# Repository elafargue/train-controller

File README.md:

train-controller
================

A Z scale model train controller with web interface.

You will find detailed instructions at http://www.aerodynes.org/ . This repository includes both hardware design files and the software you need to build the complete project.

The whole system is working well, and has been running for a long time on an actual layout.

Repository structure:

arduino: arduino sketches for the train controller hardware
hardware: schematics, boards (Eagle)
server: the node.js server that interfaces with the controller and serves the web app

Installation:

Please refer to http://www.aerodynes.org/ for detailed installation instructions. Below is a quick summary:

- Build the cape - Eagle files are included, all components are referenced in the design file, it is fairly straightforward.
- Install the arduino firmware on the cape: you can use the very good "ino" command line interface for doing so.
- Install Ubuntu Linux on your Beaglebone Black
- Install the latest nodejs distribution, and clone this repository
- Install mongodb (Ubuntu package is fine)
- Run "npm install" then "node server.js"
- ... you should be set!

Credits:

Thanks to the creators of the PID and aJson libraries (be sure to use the latest aJson library as I contributed patches to make it more robust).
Thanks to Christophe Coenraets for his great tutorials which were used as a base for the server

License:

All original code is placed under GPLv3 unless stated otherwise, see relevant license files where appropriate.

# Run as a service

Use `resources/train-controller.service` and copy it to `/etc/systemd/system`, then:

```
$ sudo systemctl daemon-reload
$ sudo systemctl enable train-controller
Created symlink /etc/systemd/system/multi-user.target.wants/train-controller.service → /etc/systemd/system/train-controller.service.
$ sudo service train-controller start
```

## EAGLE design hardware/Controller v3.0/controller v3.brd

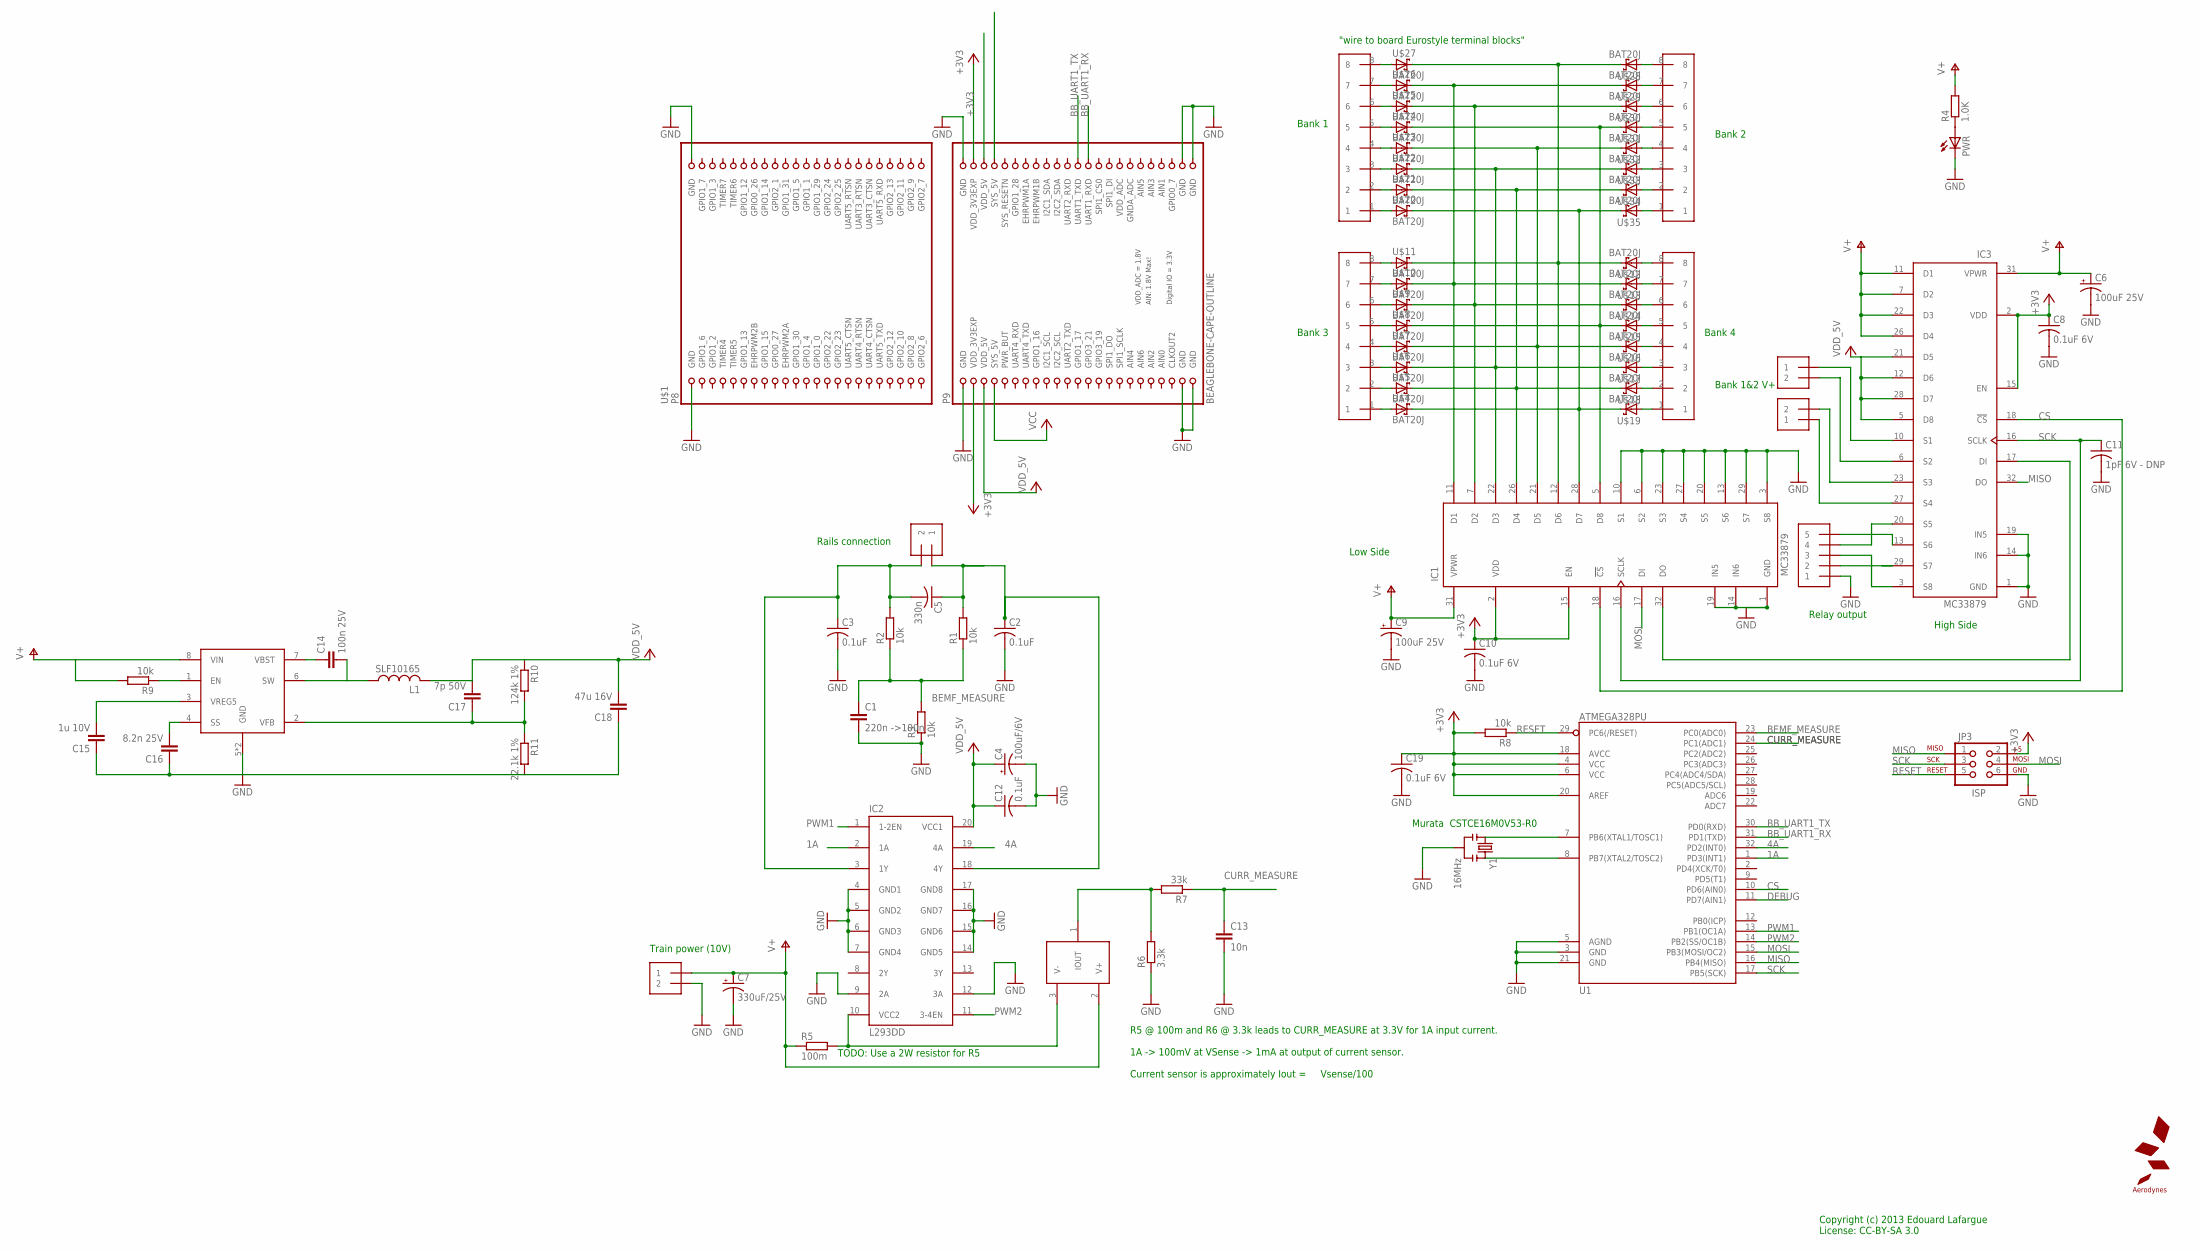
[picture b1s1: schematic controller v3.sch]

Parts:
BANK12, BANK34: 1X2-3.5MM
C1: 220n ->100n; C0805
C2, C3, C12: 0.1uF; C025-025X050
C4: 100uF/6V; E2,5-5
C5: 330n; C050-025X075
C6, C9: 100uF 25V; E2,5-6E
C7: 330uF/25V; E3,5-8
C8, C10: 0.1uF 6V; C025-025X050
C11: 1pF 6V - DNP; C0805K
C13: 10n; C0805K
C14: 100n 25V; C0805K
C15: 1u 10V; C0603K
C16: 8.2n 25V; C0603K
C17: 7p 50V; C0805K
C18: 47u 16V; C1210K
C19: 0.1uF 6V; C0603K
CON1, CON2, CON3, CON4: 1X08-CONN3.5MM; 1X08-3.5MM
CUR_SENSE: ZXCT1009-F; SOT23-1TOP
IC1, IC3: MC33879; 32SOICW-EP-065PITCH
IC2: L293DD; SOIC20-2
J1: 1X5; 1X05-3.5MM
JP3: ISP; 2X3
L1: SLF10165
PWR: LED3MM
R1, R2, R3, R8, R9: 10k; R0603
R4: 1.0K; R0603
R5: 100m; M1206
R6: 3.3k; R0603
R7: 33k; R0603
R10: 124k 1%; R0603
R11: 22.1k 1%; R0603
SL1, SL2: 1X2-3.5MM
U1: ATMEGA328PU; TQFP32-08
U$1: BEAGLEBONE-CAPE-OUTLINE; BEAGLEBONE_NOCUT
U$2: LOGO-AERODYNESSMALL; LOGO-AERODYNES-S
U$4, U$5, U$6, U$7, U$8, U$9, U$10, U$11, U$12, U$13, U$14, U$15, U$16, U$17, U$18, U$19, U$20, U$21, U$22, U$23, U$24, U$25, U$26, U$27, U$28, U$29, U$30, U$31, U$32, U$33, U$34, U$35: BAT20J; SOD-323F
U$36: TPS54327DDA; SOIC8-DDA
Y1: 16MHz; RESONATOR-SMD

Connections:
1A: IC2.2 (1A), U1.1 (PD3(INT1))
1Y: C3.1, C5.2, IC2.3 (1Y), R2.2, SL1.2
4A: IC2.19 (4A), U1.32 (PD2(INT0))
4Y: C2.1, C5.1, IC2.18 (4Y), R1.2, SL1.1
+3V3: C8.1, C10.1, C19.1, IC1.2 (VDD), IC1.15 (EN), IC3.2 (VDD), IC3.15 (EN), JP3.2, R8.2, U1.4 (VCC), U1.6 (VCC), U1.18 (AVCC), U1.20 (AREF), U$1.P9-3 (VDD_3V3EXP), U$1.P9-4 (VDD_3V3EXP)
BB_UART1_RX: U1.31 (PD1(TXD)), U$1.P9-26 (UART1_RXD)
BB_UART1_TX: U1.30 (PD0(RXD)), U$1.P9-24 (UART1_TXD)
BEMF_MEASURE: C1.1, R1.1, R2.1, R3.2, U1.23 (PC0(ADC0))
CS: IC1.18 (!CS), IC3.18 (!CS), U1.10 (PD6(AIN0))
CURR_MEASURE: C13.1, R7.1, U1.24 (PC1(ADC1))
DEBUG: U1.11 (PD7(AIN1))
GND: C1.2, C2.2, C3.2, C4.-, C6.-, C7.-, C8.2, C9.-, C10.2, C11.2, C12.2, C13.2, C15.1, C16.1, C18.1, C19.2, IC1.1 (GND), IC1.3 (S8), IC1.6 (S2), IC1.10 (S1), IC1.13 (S6), IC1.14 (IN6), IC1.19 (IN5), IC1.20 (S5), IC1.23 (S3), IC1.27 (S4), IC1.29 (S7), IC2.4 (GND1), IC2.5 (GND2), IC2.6 (GND3), IC2.7 (GND4), IC2.9 (2A), IC2.12 (3A), IC2.14 (GND5), IC2.15 (GND6), IC2.16 (GND7), IC2.17 (GND8), IC3.1 (GND), IC3.14 (IN6), IC3.19 (IN5), J1.1, JP3.6, PWR.K (C), R3.1, R6.1, R11.2, SL2.2, U1.3 (GND), U1.5 (AGND), U1.21 (GND), U$1.P8-1 (GND), U$1.P8-2 (GND), U$1.P9-1 (GND), U$1.P9-2 (GND), U$1.P9-43 (GND), U$1.P9-44 (GND), U$1.P9-45 (GND), U$1.P9-46 (GND), U$36.5 (GND), U$36.PAD (GND), Y1.2
GNDA_ADC: U$1.P9-34 (GNDA_ADC)
MISO: IC3.32 (DO), JP3.1, U1.16 (PB4(MISO))
MOSI: IC1.17 (DI), JP3.4, U1.15 (PB3(MOSI/OC2))
unnamed: BANK34.1, IC3.27 (S4)
unnamed: BANK34.2, IC3.23 (S3)
unnamed: BANK12.2, IC3.6 (S2)
unnamed: BANK12.1, IC3.10 (S1)
unnamed: CUR_SENSE.3 (V-), IC2.10 (VCC2), R5.2
unnamed: CUR_SENSE.1 (IOUT), R6.2, R7.2
unnamed: IC1.22 (D3), U$6.C, U$17.C, U$22.C, U$33.C
unnamed: IC1.21 (D5), U$7.C, U$16.C, U$23.C, U$32.C
unnamed: IC1.5 (D8), U$8.C, U$15.C, U$24.C, U$31.C
unnamed: CON3.3, U$6.A
unnamed: IC1.28 (D7), U$4.C, U$19.C, U$20.C, U$35.C
unnamed: IC1.12 (D6), U$11.C, U$12.C, U$27.C, U$28.C
unnamed: IC1.32 (DO), IC3.17 (DI)
unnamed: IC1.11 (D1), U$10.C, U$13.C, U$26.C, U$29.C
unnamed: IC1.26 (D4), U$5.C, U$18.C, U$21.C, U$34.C
unnamed: IC1.7 (D2), U$9.C, U$14.C, U$25.C, U$30.C
unnamed: IC3.20 (S5), J1.4
unnamed: CON3.2, U$5.A
unnamed: CON3.1, U$4.A
unnamed: CON3.8, U$11.A
unnamed: CON3.7, U$10.A
unnamed: CON3.6, U$9.A
unnamed: CON3.5, U$8.A
unnamed: CON3.4, U$7.A
unnamed: CON4.8, U$12.A
unnamed: CON4.7, U$13.A
unnamed: CON4.6, U$14.A
unnamed: CON4.5, U$15.A
unnamed: CON4.4, U$16.A
unnamed: CON4.3, U$17.A
unnamed: CON4.2, U$18.A
unnamed: CON4.1, U$19.A
unnamed: CON1.8, U$27.A
unnamed: CON1.7, U$26.A
unnamed: PWR.A, R4.1
unnamed: CON1.6, U$25.A
unnamed: CON1.5, U$24.A
unnamed: CON1.4, U$23.A
unnamed: CON1.3, U$22.A
unnamed: CON1.2, U$21.A
unnamed: CON1.1, U$20.A
unnamed: CON2.8, U$28.A
unnamed: CON2.7, U$29.A
unnamed: CON2.6, U$30.A
unnamed: CON2.5, U$31.A
unnamed: CON2.4, U$32.A
unnamed: CON2.3, U$33.A
unnamed: CON2.2, U$34.A
unnamed: CON2.1, U$35.A
unnamed: IC3.13 (S6), J1.5
unnamed: IC3.29 (S7), J1.2
unnamed: IC3.3 (S8), J1.3
unnamed: U1.7 (PB6(XTAL1/TOSC1)), Y1.1
unnamed: U1.8 (PB7(XTAL2/TOSC2)), Y1.3
unnamed: R9.1, U$36.1 (EN)
unnamed: C14.1, U$36.7 (VBST)
unnamed: C16.2, U$36.4 (SS)
unnamed: C14.2, L1.P$1 (1), U$36.6 (SW)
unnamed: C15.2, U$36.3 (VREG5)
unnamed: C17.1, R10.2, R11.1, U$36.2 (VFB)
PWM1: IC2.1 (1-2EN), U1.13 (PB1(OC1A))
PWM2: IC2.11 (3-4EN), U1.14 (PB2(SS/OC1B))
RESET: JP3.5, R8.1, U1.29 (PC6(/RESET))
SCK: C11.1, IC1.16 (SCLK), IC3.16 (SCLK), JP3.3, U1.17 (PB5(SCK))
SYS_5V: U$1.P9-7 (SYS_5V), U$1.P9-8 (SYS_5V)
V+: C6.+, C7.+, C9.+, CUR_SENSE.2 (V+), IC1.31 (VPWR), IC3.7 (D2), IC3.11 (D1), IC3.22 (D3), IC3.26 (D4), IC3.31 (VPWR), R4.2, R5.1, R9.2, SL2.1, U$36.8 (VIN)
VDD_5V: C4.+, C12.1, C17.2, C18.2, IC2.20 (VCC1), IC3.5 (D8), IC3.12 (D6), IC3.21 (D5), IC3.28 (D7), L1.P$2 (2), R10.1, U$1.P9-5 (VDD_5V), U$1.P9-6 (VDD_5V)
VDD_ADC: U$1.P9-32 (VDD_ADC)

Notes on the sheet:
Rails connection
Train power (10V)
Low Side
High Side
Bank 1
Bank 2
Bank 1&2 V+
Bank 3
Bank 4
"wire to board Eurostyle terminal blocks"
R5 @ 100m and R6 @ 3.3k leads to CURR_MEASURE at 3.3V for 1A input current. 1A -> 100mV at VSense -> 1mA at output of current sensor. Current sensor is approximately Iout = Vsense/100
Copyright (c) 2013 Edouard Lafargue License: CC-BY-SA 3.0
TODO: Use a 2W resistor for R5
Relay output
Murata CSTCE16M0V53-R0

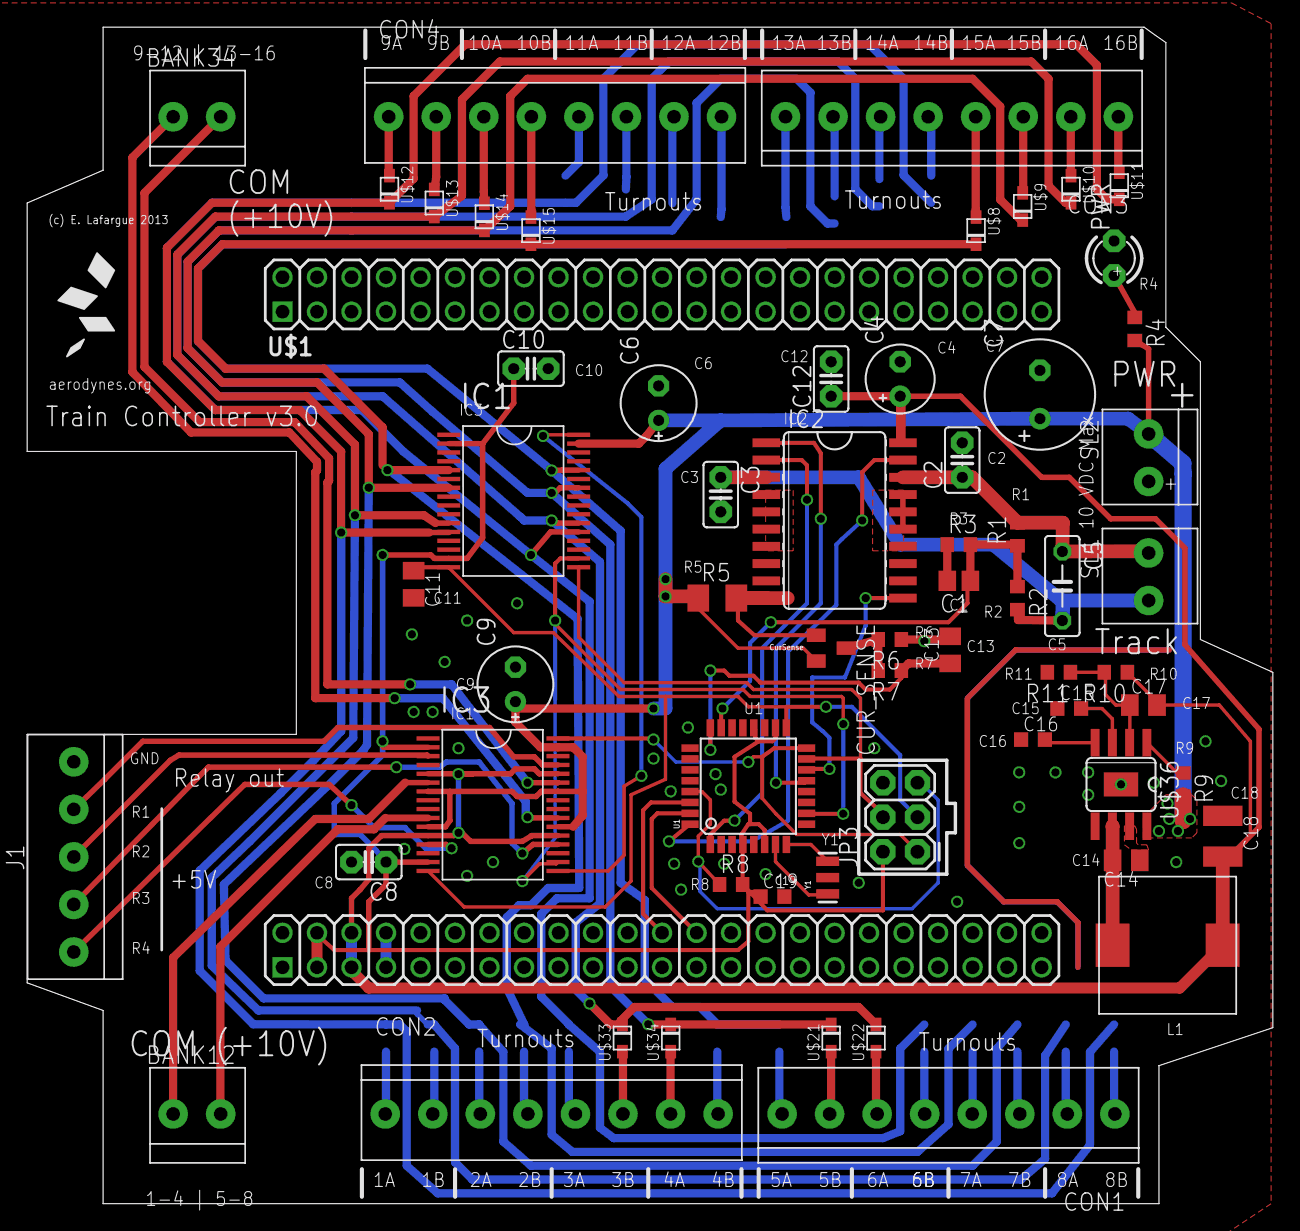
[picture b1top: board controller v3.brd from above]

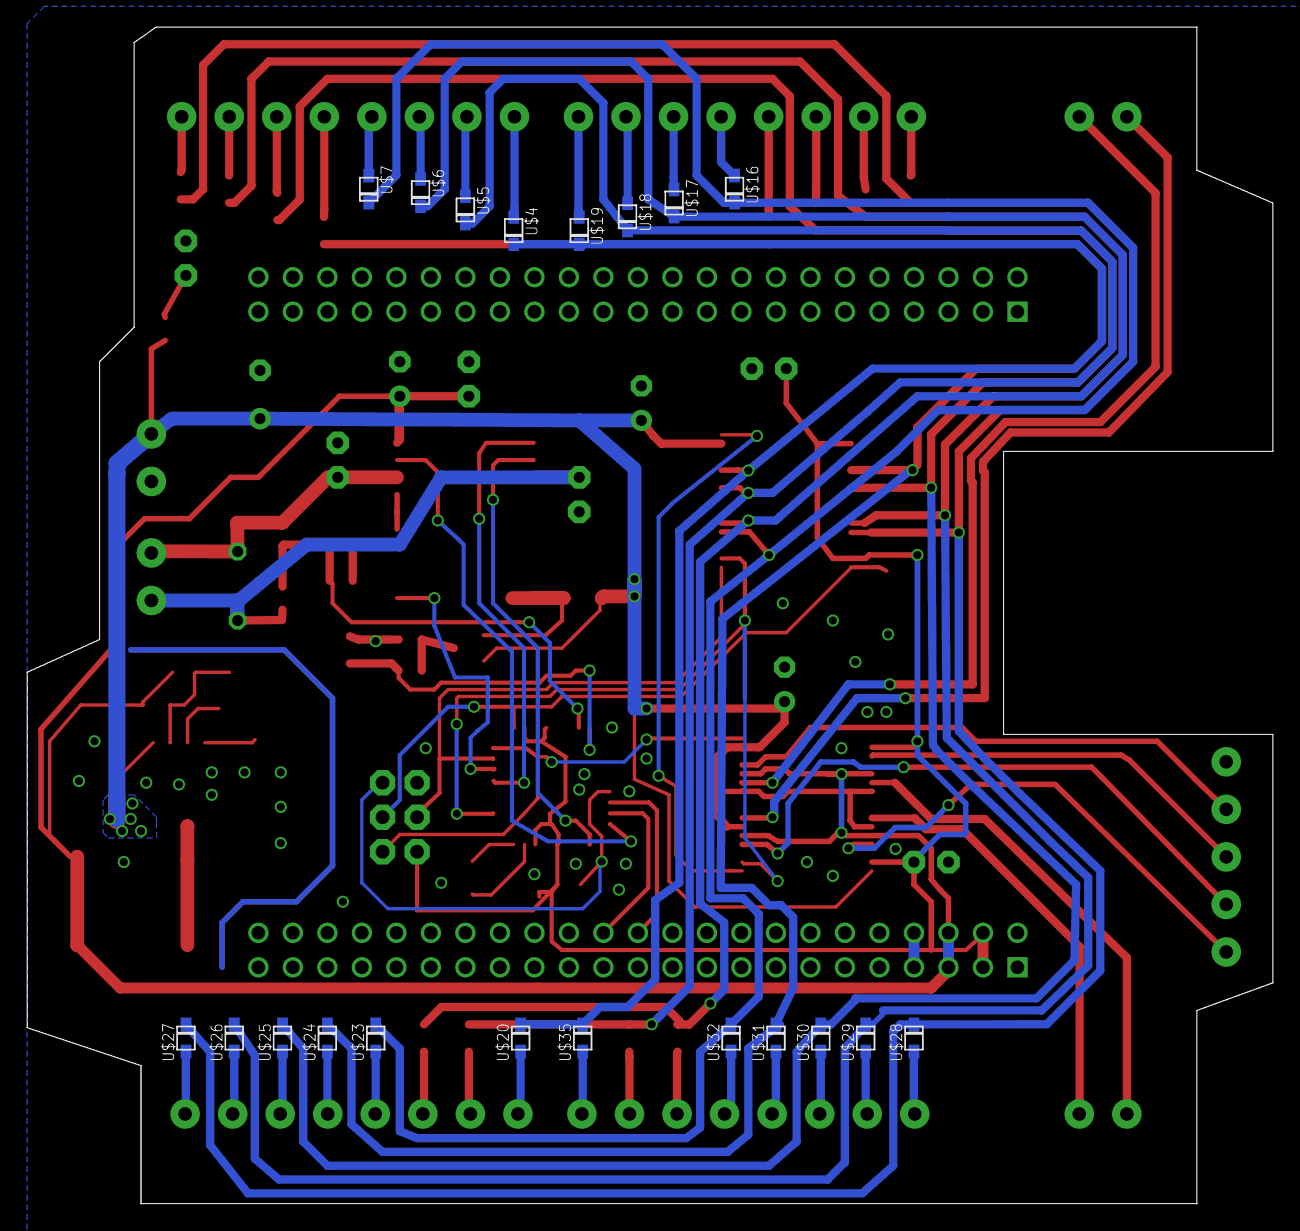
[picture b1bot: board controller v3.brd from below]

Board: 2 copper layers, 91.7 x 86.6 mm, 83 parts (20 on the bottom side), 80 nets.

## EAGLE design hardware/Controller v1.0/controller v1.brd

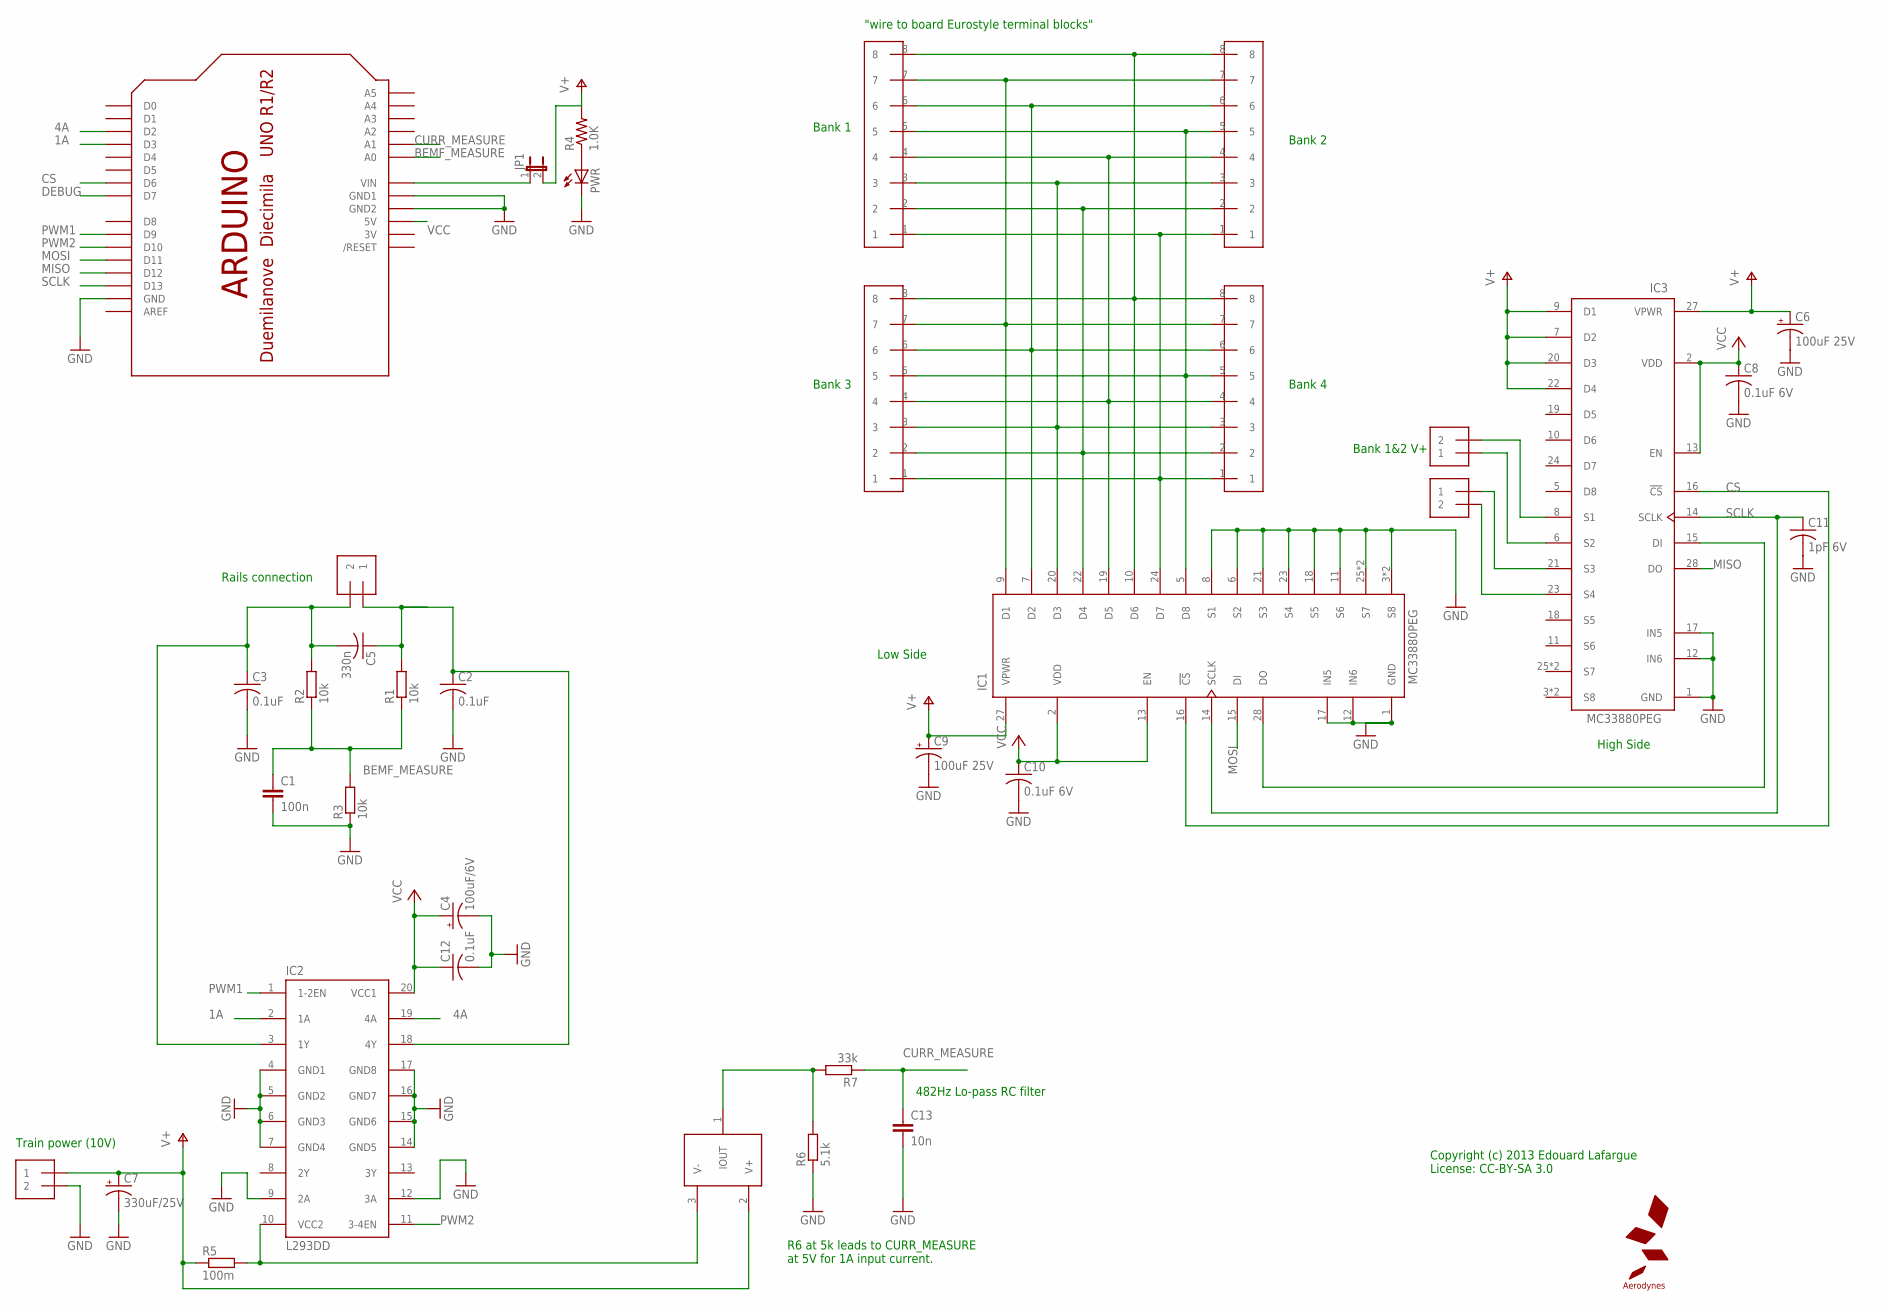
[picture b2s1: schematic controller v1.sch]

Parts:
BANK12, BANK34: 1X2-3.5MM
C1: 100n; C0805
C2, C3, C12: 0.1uF; C025-025X050
C4: 100uF/6V; E2,5-5
C5: 330n; C050-025X075
C6, C9: 100uF 25V; E2,5-6E
C7: 330uF/25V; E2,5-6
C8, C10: 0.1uF 6V; C025-025X050
C11: 1pF 6V; C0805K
C13: 10n; C0805K
CON1, CON2, CON3, CON4: 1X08-CONN3.5MM; 1X08-3.5MM
IC1, IC3: MC33880PEG; SO28W
IC2: L293DD; SOIC20-2
JP1: JP1E; JP1
PWR: LED3MM
R1, R2, R3: 10k; R0805
R4: 1.0K; M0805
R5: 100m; M1206
R6: 5.1k; R0603
R7: 33k; R0603
SL1, SL2: 1X2-3.5MM
U$1: ARDUINO; ARDUINO-NOCUT
U$2: LOGO-AERODYNESSMALL; LOGO-AERODYNES-S
U$3: ZXCT1009-F; SOT23-1TOP

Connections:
1A: IC2.2 (1A), U$1.D3
1Y: C3.1, C5.2, IC2.3 (1Y), R2.2, SL1.2
3V: U$1.3V
4A: IC2.19 (4A), U$1.D2
4Y: C2.1, C5.1, IC2.18 (4Y), R1.2, SL1.1
BEMF_MEASURE: C1.1, R1.1, R2.1, R3.2, U$1.A0
CS: IC1.16 (!CS), IC3.16 (!CS), U$1.D6
CURR_MEASURE: C13.1, R7.1, U$1.A1
DEBUG: U$1.D7
GND: C1.2, C2.2, C3.2, C4.-, C6.-, C7.-, C8.2, C9.-, C10.2, C11.2, C12.2, C13.2, IC1.1 (GND), IC1.3 (S8), IC1.4 (S8), IC1.6 (S2), IC1.8 (S1), IC1.11 (S6), IC1.12 (IN6), IC1.17 (IN5), IC1.18 (S5), IC1.21 (S3), IC1.23 (S4), IC1.25 (S7), IC1.26 (S7), IC2.4 (GND1), IC2.5 (GND2), IC2.6 (GND3), IC2.7 (GND4), IC2.9 (2A), IC2.12 (3A), IC2.14 (GND5), IC2.15 (GND6), IC2.16 (GND7), IC2.17 (GND8), IC3.1 (GND), IC3.12 (IN6), IC3.17 (IN5), PWR.K (C), R3.1, R6.1, SL2.2, U$1.GND, U$1.GND1, U$1.GND2
MISO: IC3.28 (DO), U$1.D12
MOSI: IC1.15 (DI), U$1.D11
unnamed: BANK34.2, IC3.23 (S4)
unnamed: BANK34.1, IC3.21 (S3)
unnamed: BANK12.1, IC3.6 (S2)
unnamed: BANK12.2, IC3.8 (S1)
unnamed: IC2.10 (VCC2), R5.2, U$3.3 (V-)
unnamed: R6.2, R7.2, U$3.1 (IOUT)
unnamed: CON1.3, CON2.3, CON3.3, CON4.3, IC1.20 (D3)
unnamed: CON1.4, CON2.4, CON3.4, CON4.4, IC1.19 (D5)
unnamed: CON1.5, CON2.5, CON3.5, CON4.5, IC1.5 (D8)
unnamed: JP1.1, U$1.VIN
unnamed: CON1.1, CON2.1, CON3.1, CON4.1, IC1.24 (D7)
unnamed: CON1.8, CON2.8, CON3.8, CON4.8, IC1.10 (D6)
unnamed: IC1.28 (DO), IC3.15 (DI)
unnamed: CON1.7, CON2.7, CON3.7, CON4.7, IC1.9 (D1)
unnamed: CON1.2, CON2.2, CON3.2, CON4.2, IC1.22 (D4)
unnamed: CON1.6, CON2.6, CON3.6, CON4.6, IC1.7 (D2)
unnamed: PWR.A, R4.1
PWM1: IC2.1 (1-2EN), U$1.D9
PWM2: IC2.11 (3-4EN), U$1.D10
SCLK: C11.1, IC1.14 (SCLK), IC3.14 (SCLK), U$1.D13
V+: C6.+, C7.+, C9.+, IC1.27 (VPWR), IC3.7 (D2), IC3.9 (D1), IC3.20 (D3), IC3.22 (D4), IC3.27 (VPWR), JP1.2, R4.2, R5.1, SL2.1, U$3.2 (V+)
VCC: C4.+, C8.1, C10.1, C12.1, IC1.2 (VDD), IC1.13 (EN), IC2.20 (VCC1), IC3.2 (VDD), IC3.13 (EN), U$1.5V

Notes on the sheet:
Rails connection
Train power (10V)
Low Side
High Side
Bank 1
Bank 2
Bank 1&2 V+
Bank 3
Bank 4
"wire to board Eurostyle terminal blocks"
R6 at 5k leads to CURR_MEASURE at 5V for 1A input current.
Copyright (c) 2013 Edouard Lafargue License: CC-BY-SA 3.0
482Hz Lo-pass RC filter

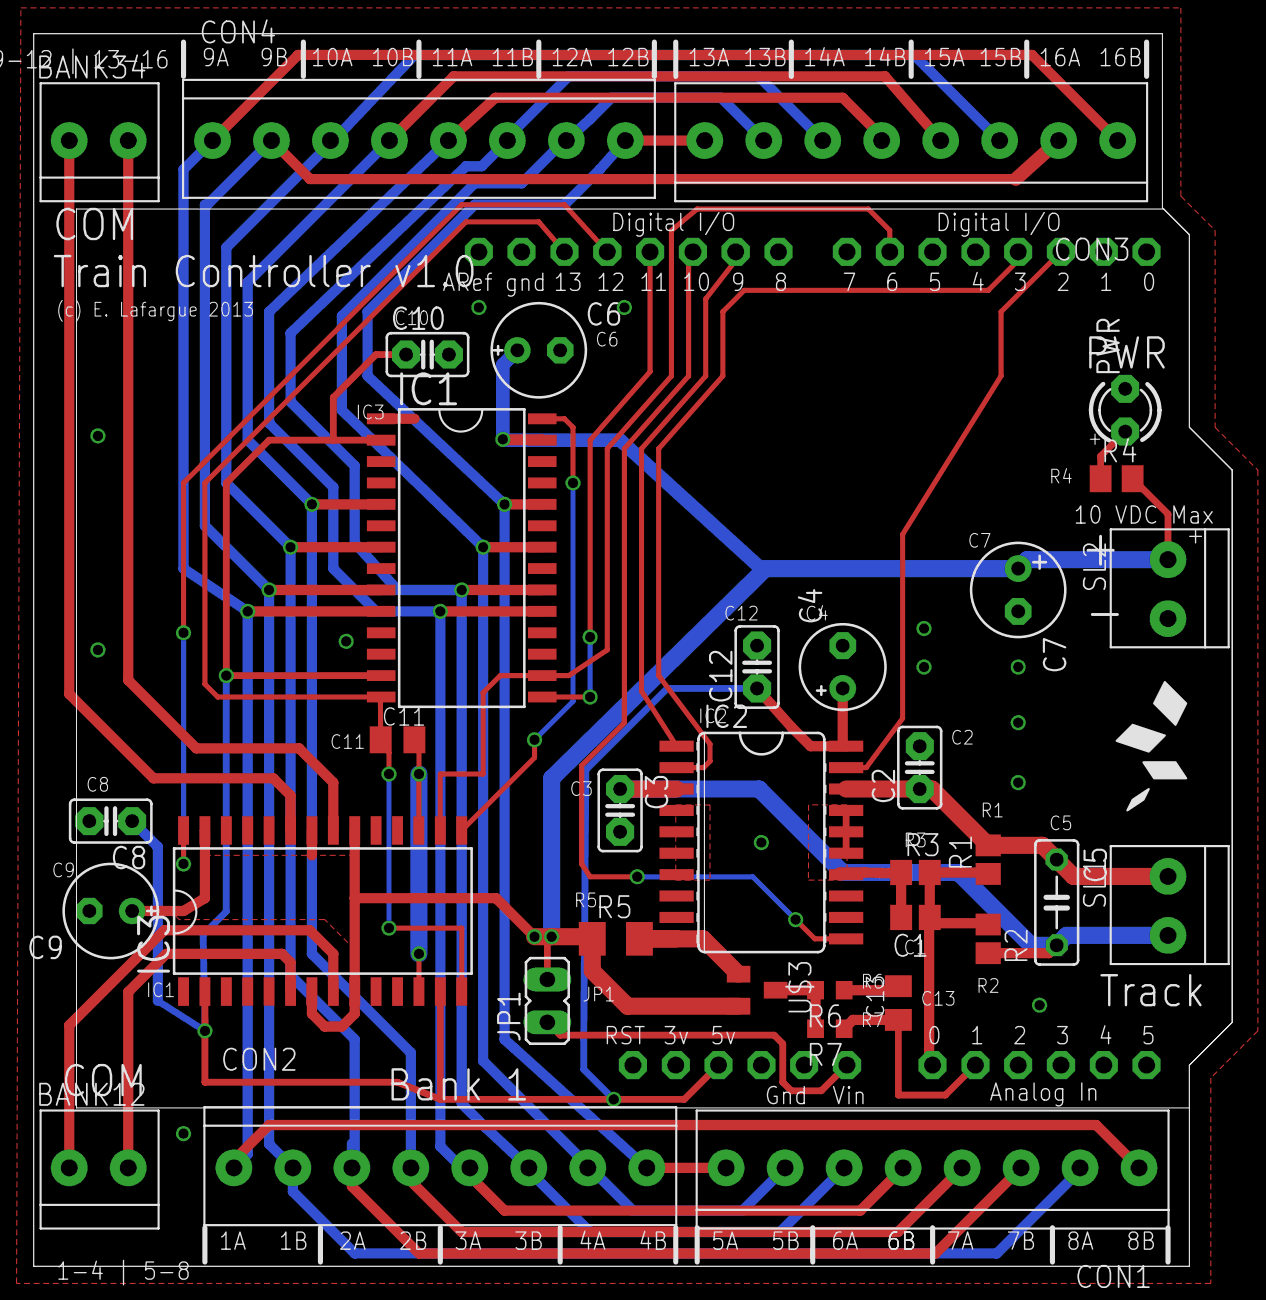
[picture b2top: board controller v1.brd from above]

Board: 2 copper layers, 71.1 x 73.1 mm, 36 parts (0 on the bottom side), 32 nets.

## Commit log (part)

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2013-02-07 Initial controller sketch for Arduino
2013-02-08 JSON and Hardware schematics
    This is untested so far. Added JSON support for both input and output
    on the controller, added simple schematics of the controller, updated
    .gitignore to exclude Eagle backup files.
2013-02-09 Working version of JSON interface
    The Arduino board tends to lose characters on the serial input,
    so more work is needed to make it more reliable. But it already
    works quite well.
2013-02-09 Lowered default speed, added free ram debug output
    Now seems to reliably get commands every time, since interrupts
    are now faster and serial speed slower. Also debugs the amount of
    free RAM in output if "DEBUG" is defined.
2013-02-09 Debug web page
    Added a debug.html web page to display controller parameters and graph
    them in real time. Only listens, does not send commands yet.
2013-02-09 Ignore more Mac-specific extensions
2013-02-10 Progress on web app
    Basic architecture for the web app. So far no real functionality, it is
    nearly identical to Christophe Coenraets' Wine Cellar. More to follow.
2013-02-10 Start using mongoose for database management
    Mongoose makes it much easier to manage the database. Migrated the
    locomotives to use it.
2013-02-10 Layouts defined and schema updated
    Progress on the schema for the application - still in flux - as well
    as a very basic layout browser.
2013-02-11 Manage settings on server through REST call /settings
    Implemented a single setting object on the database
2013-02-11 Select loco and layout
    Application now correctly selects locomotive and layout, and updates
    the settings. Settings page shows debug info on the settings object.
2013-02-12 General update of web app.
    In no particular order:
    - Layout/loco image drag and drop now works
    - Home view now is ready to update itself when loco and layouts are chosen
    - Settings view gives debugging and settings clear options
    - Better loco and layout list look and feel
2013-02-12 Enable Add Loco / Add Layout in Loco/Layout select screen
    Title says it all.
2013-02-13 Layout editor can now create and edit controllers
    Used a composite view since we can have many controllers on a single
    layout (might limit this later). Still details to iron out such as
    model validation before save for controller fields, etc.
2013-02-13 Further work on controller create/edit/delete from inside of layout view
    A bit tricky, but now it seems to be working fine every time.
2013-02-13 Forgot one file in previous commit
2013-02-17 Web app now talks to controller.
    Still work in progress, but initial messaging between web app and controller
    hardware is working, and several subviews can receive updates from the
    controller simultaneously.
    Error checking and overall robustness still to improve.
2013-02-21 Manage application settings properly
    Web app now manages settings/state using the same shared settings
    model between views (passed from appplicatino router on main.js), this
    way we get the correct change events, especially in the home view.
2013-02-22 Bug fixes
    - When adding a new logo and selecting the picture at the same time
    the picture was called "undefined" instead of loco Id. Fixed
    - Adding a new loco was not working because of reference to _id in
    template.
    - Removed references to localhost in all socket.io calls.
2013-02-22 Fix Graph initialisation + add License notices
    Finally fixed initialisation problem with flot. Also added GPL
    license info in the relevant places.
2013-02-24 Add feeback to direction buttons
2013-02-27 Add confirm delete button on both loco and layout managers
    Used bootbox.js as a helper library.
2013-03-01 Implement removeListener on link manager.
    So that entities like the loco controller don't get multiple
    subscriptions to the same event.
2013-03-01 Bug fix: switch to FuelUX caused edit loco and layout to fail.
    Also small progress on PID settings UI
2013-03-02 Backtrack: FuelUX did not work as well as expected.
    Used a dedicated bootstrap numeric spinner instead. More lightweight
    and actually works, whereas the FuelUX spinner did not work for decimal
    places at all - tons of weird bugs.
2013-03-04 Arduino sketch update: add command ack name
    The arduino controller now adds the command name to ack packets
    so that the server knows what it is acknowledging for.
2013-03-05 Add touch support for power control slider
    Now works fine with finger drag - and page does not scroll -
2013-03-05 Bugfix - when power=0, progress slider did not get updated
    was testing for value, not for isNaN...
2013-03-05 Don't glow non-clickable thumbnails
2013-03-05 Better usability on train controller - better user feedback
    Now various parts get enabled/disabled when they can/cannot be used.
2013-03-06 Web application support for accessories - start.
    Layouts can now manage a list of 'accessories' (turnouts, slips, etc). Those
    are saved in the database, and displayed on the layout image on the main screen.
    accessories can be dragged to their correct location on the layout image, and that
    location is saved in the database too.
2013-03-08 Bugfixing arduino sketch
    Latch values were wrong earlier.
2013-03-08 Improvements on layout edit view.
    Pressing "Enter" on a modal now triggers the default function (blue button)
    rather than just close the modal and do nothing. Fixed error in new accessory
    creation.
2013-03-08 Snap to grid when dragging accessories... but only works on Chrome somehow!
    I don't know what's going on with Firefox...
2013-03-08 Compute grid size based on percentage of layout image
    This way we get more consistent snap to grid for various window sizes.
2013-03-13 Manage uncouplers
    "Uncouplers" are special tracks for uncoupling cars. The layout details
    view can now configure an accessory to be an uncoupler, and attribute both
    address and port to the uncoupler. This way the same address can manage two
    uncoupler accessories and no I/O is wasted.
2013-03-14 Manage a log book for locomotives
    In the loco edit menu, you can now add/remove/edit logbook entries to keep
    track of maintenance tasks. Very simple logbook, nothing fancy.
    Note: I used backbone collections to manage the logbook entries, a bit different
    from what i have been doing with accessories and controllers so far. No major
    added interest, this method also means that we need to delete logbook entries
    manually whenever a locomotive is deleted. An alternative would be to manage a logbook
2013-03-17 Responsive design part 2
    Missed two files in last commit, typical.
2013-03-18 Big bugfix on hardware controller schematics and board.
    The 33880 pinout was reversed on my schematics...
2013-03-20 Final hardware version (Arduino shield) firmware working
    No current measurement yet though.
2013-03-20 Diagnostics view in web app
    Now that the harware can run power on tests and detect whether an accessory
    is connected or not, created a diags screen in the web app to display this.
2013-03-22 Diagnostics screen works now!
    Complete board diagnostics, including port open circuit detection.
2013-03-23 V1.0 Hardware - Arduino Shield as ordered on Seeed Studio
    Added the Eagle + Gerbers ordered on Seeed Studio - not tested yet
    obviously.
2013-03-25 Bug: could not add a new layout after latest changes to link manager
2013-04-02 Add last maintenance time in main screen.
2013-04-08 Start of Beaglebone cape
2013-04-08 Further work on backup of settings
2013-04-08 Debug output for server.js (raw Hex)
2013-04-09 Disable port diags if POST result is Fail for SPI
2013-04-09 Bugfix on opacity
2013-04-15 Updates to match exactly first working prototype
2013-04-15 Better port open status display on diag screen
    now uses a 1a/1b 2a/2b system, rather than counting from
    1 to 32, so this matches what's printed on the PCB...
2013-04-16 Backup and restore of configuration implemented, test in progress.
2013-05-05 Remove harcoded dependency on older socket.io lib.
2013-05-05 Use latest tarball snapshot of SerialPort
2013-05-13 Add test buttons on accessory settings
2013-05-13 Small typo corrections
2013-05-14 Add support for current sensor.
    All values output by the controller are now in real units (mV for BEMF
    and mA for current). Web app graphs current value. Better graphs (no
    gaps when sending turnout commands).
2013-05-15 Oops...
2013-05-16 Make graph axes the same color as the lines
    Now the user can understand which graph axis matches which line...
2013-05-16 Add Car management in the web app
    The cars manager is just a database of cars, does not (yet) have any
    use in running the layout.
2013-05-16 Set accessory pulse length upon controller connection
2013-05-22 Autosave runtime every 10 seconds when running a loco.
2013-05-22 Send PID params upon controller connection
2013-05-23 Bugfixes on log management And display log journal in loco details.
2013-05-28 Add view switcher + full screen graphs
    Refactoring: now uses a clean way to switch views with call to
    "onClose" function in the views, for proper cleanup.
    Added a "Full screen graph" view on Diagnostics screen.
2013-05-28 Cleanup on view switcher for all views
2013-06-26 Hardware controller: Beaglebone cape
    This is the working design - v3.0. Not fully debugged yet, but seems
    to be working fine so far.
2013-08-04 Various updates and bug fixes
2013-08-04 Relay query in accessory view: bugfixes
2013-08-19 Maintenance and improvements:
    Does not crash on DB server not running - just waits for it to come up.
    Better accessory settings handling when changing accessory type in settings.
    Cleaned up README and About.
2015-03-17 Node-serialport fixes for current version.
2015-03-17 Fix for CSS
2015-03-18 PouchDB fix: some numeric values are now returned as strings, use parseFloat.
2015-03-18 Arduino Sketch: fix auto accessory off (was not working properly, and accessories remained on forever).
2015-03-18 Accessory control bugfix (on was not sent)
2019-11-02 Bump underscore.string from 2.4.0 to 3.3.5 in /server
    Bumps [underscore.string](https://github.com/epeli/underscore.string) from 2.4.0 to 3.3.5.
    - [Release notes](https://github.com/epeli/underscore.string/releases)
    - [Changelog](https://github.com/epeli/underscore.string/blob/master/CHANGELOG.markdown)
    - [Commits](https://github.com/epeli/underscore.string/compare/2.4.0...3.3.5)
2022-04-10 Raspberry Pi adapter board to make the controller compatible with RPi 3
2025-08-14 More updates to HTML templates
2025-08-15 Restore proper views for the layout/loco/car lists
2025-08-15 Fix picture upload
2025-08-15 Restore ability to select a layout
2025-08-15 Improve accessory details view
2025-08-15 Add more bootstrap 5 upgrades
2025-08-15 Dark/Light mode support
2025-08-15 Working theme support
2025-08-15 Fix controller rendering
2025-08-15 Add a test controller, use with "TEST" as the port
2025-08-15 Implement serial port selection dropdown in controller details Create alerts if serial port open doesn't work as expected
2025-08-15 Remove MDB5 since it's not needed Finish (?) migration to Bootstrap 5 and remove unused CS Large update to all javascript dependencies, and serve them all locally Remove unused JavaScript libraries a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
2025-08-15 Fix display on small screens (mobile)
2025-08-15 Improve logbook display
2025-08-16 Don't let the name of the locomotives/car/layout names overflow
2025-08-16 Sort cars and locomotives by reference
    By numeric order
2025-08-16 Full upgrade (#2)
    * Claude: upgrade to Bootstrap 5, step 1
    * More updates to HTML templates
    * Further migration work
    * Restore proper views for the layout/loco/car lists
    * Fix picture upload
    * Add "Change Image" button for manual upload of images
2025-09-01 Display the locomotive image as a modal in loco details

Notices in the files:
parts and their libraries:
SparkFun: Licensing: CC v3.0 Share-Alike You are welcome to use this library for commercial purposes.
